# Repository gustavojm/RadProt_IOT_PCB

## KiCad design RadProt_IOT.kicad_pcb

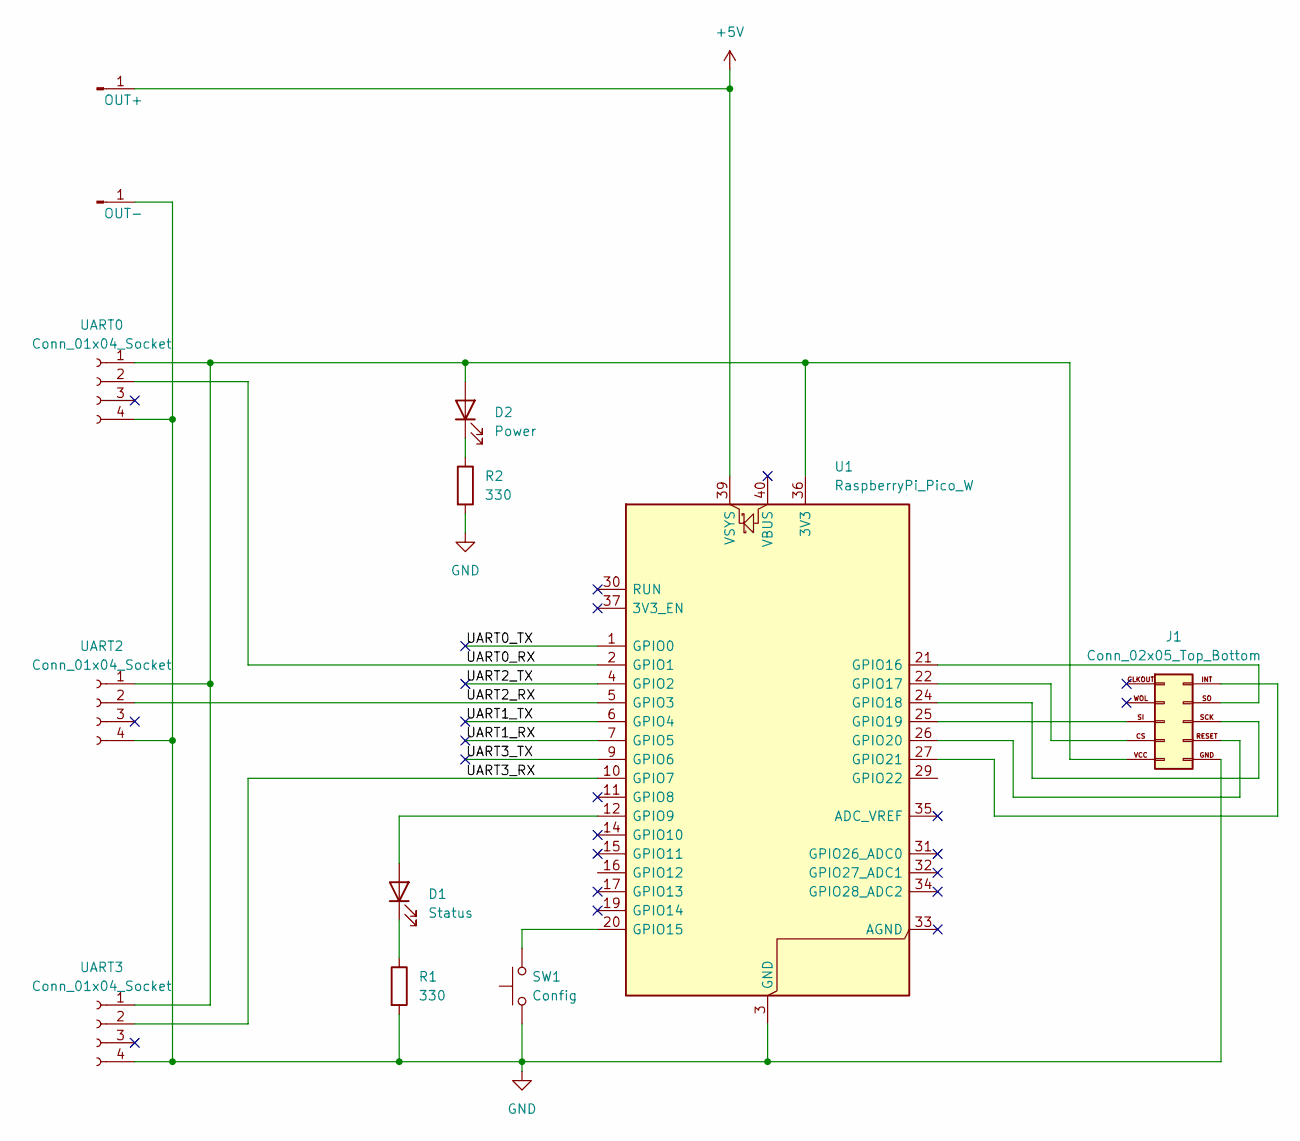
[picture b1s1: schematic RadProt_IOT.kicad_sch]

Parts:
D1: Status; LED_D3.0mm
D2: Power; LED_D3.0mm
J1: Conn_02x05_Top_Bottom; PinSocket_2x05_P2.54mm_Vertical
J5: OUT+; PinHeader_1x01_P2.54mm_Vertical
J6: OUT-; PinHeader_1x01_P2.54mm_Vertical
R1, R2: 330; R_Axial_DIN0204_L3.6mm_D1.6mm_P7.62mm_Horizontal
SW1: Config; SW_PUSH_6mm
U1: RaspberryPi_Pico_W; RaspberryPi_Pico_W_SMD_HandSolder
UART0, UART2, UART3: Conn_01x04_Socket; PinSocket_1x04_P2.54mm_Vertical

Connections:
+5V: J5.1, U1.39 (VSYS)
/UART0_RX: U1.2 (GPIO1), UART0.2
/UART0_TX: U1.1 (GPIO0)
/UART1_RX: U1.7 (GPIO5)
/UART1_TX: U1.6 (GPIO4)
/UART2_RX: U1.5 (GPIO3), UART2.2
/UART2_TX: U1.4 (GPIO2)
/UART3_RX: U1.10 (GPIO7), UART3.2
/UART3_TX: U1.9 (GPIO6)
GND: J1.GND, J6.1, R1.2, R2.2, SW1.1, U1.3 (GND), U1.8 (GND), U1.13 (GND), U1.18 (GND), U1.23 (GND), U1.28 (GND), U1.38 (GND), UART0.4, UART2.4, UART3.4
unnamed: D1.2 (A), U1.12 (GPIO9)
unnamed: D1.1 (K), R1.1
unnamed: D2.2 (A), J1.VCC, U1.36 (3V3), UART0.1, UART2.1, UART3.1
unnamed: D2.1 (K), R2.1
unnamed: SW1.2, U1.20 (GPIO15)
unnamed: J1.SO, U1.21 (GPIO16)
unnamed: J1.CS, U1.22 (GPIO17)
unnamed: J1.SCK, U1.24 (GPIO18)
unnamed: J1.SI, U1.25 (GPIO19)
unnamed: J1.RESET, U1.26 (GPIO20)
unnamed: J1.INT, U1.27 (GPIO21)

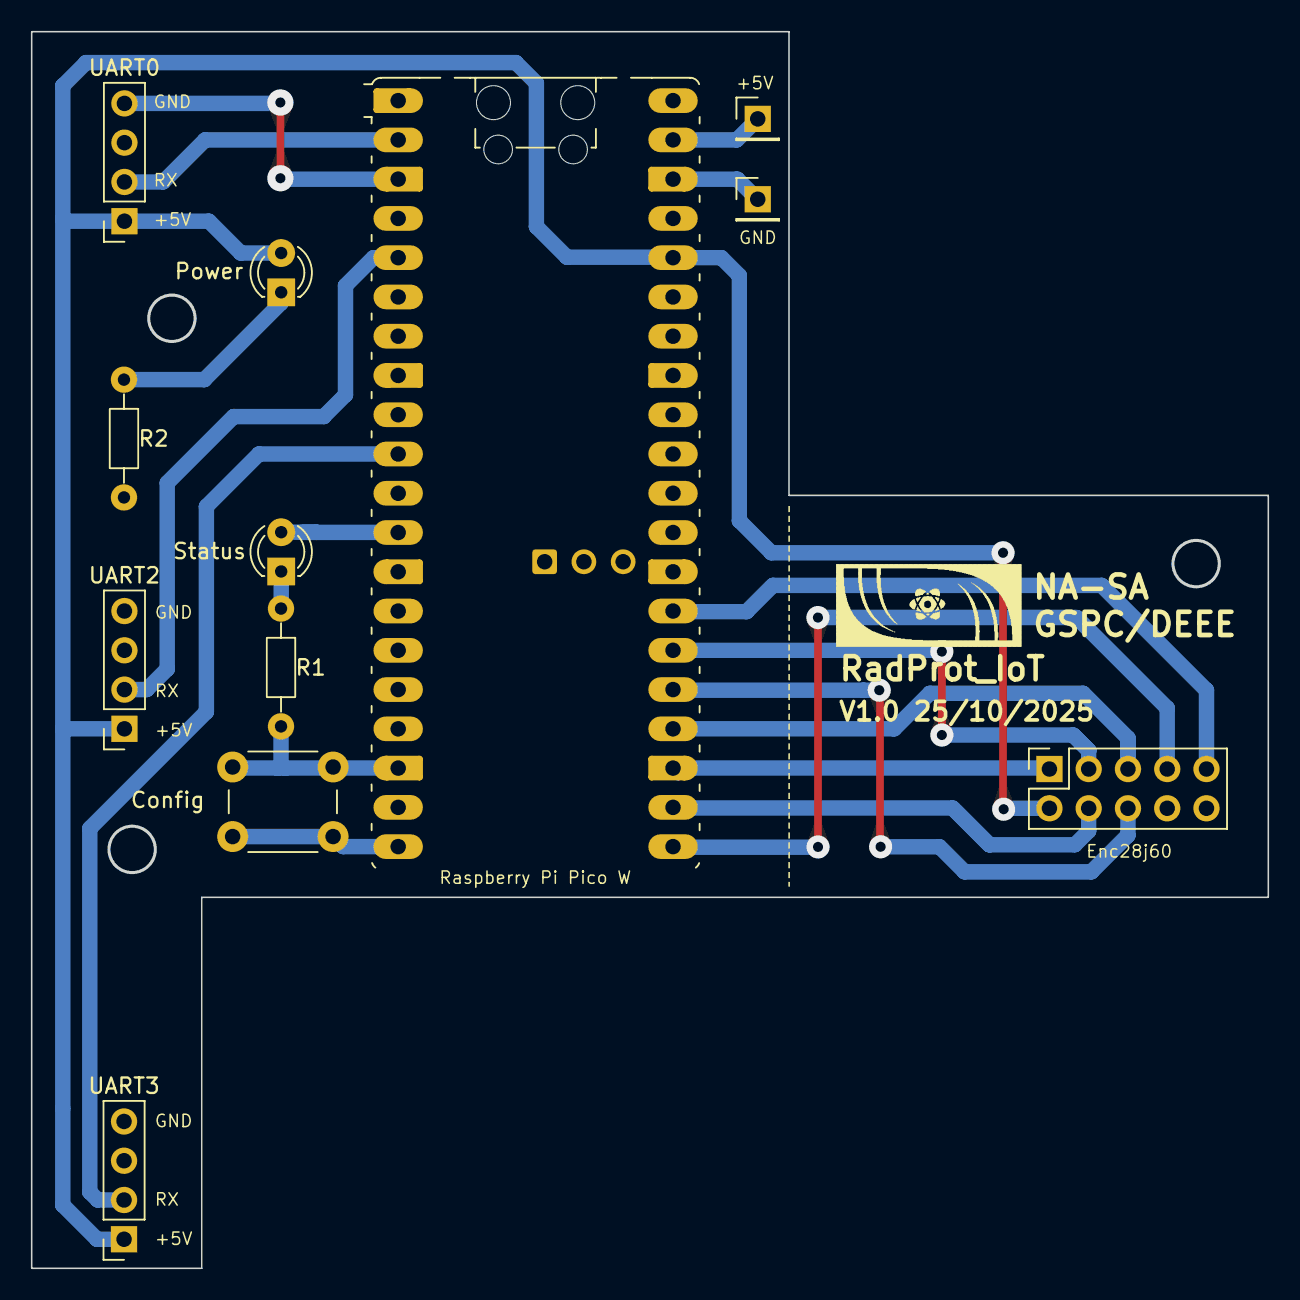
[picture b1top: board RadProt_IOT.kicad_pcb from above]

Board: 2 copper layers, 79.9 x 79.9 mm, 13 parts (0 on the bottom side), 16 nets.

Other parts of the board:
LOGO: logo_nasa

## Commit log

2025-06-25 manually routed, 1 route needs bridge
2025-06-26 routed with 1mm
2025-06-26 nice
2025-06-26 nicer
2025-06-26 nicer +10
2025-06-27 nice +20
2025-06-27 nice +30
2025-06-27 nice +40
2025-07-01 teardrops
2025-07-08 gcode generated...
2025-07-23 prepared univprepared universal board with this layout
2025-07-29 modified one pad of raspberry pi
2025-07-29 added Power Ledd
2025-07-31 to Cristian
2025-10-08 powering max3232's from 3V3 (RPi Pico's internal SMPS)
2025-10-08 changed some labels
2025-10-27 added logo and changed hole sizes from 0.65 to 0.8
2025-10-27 chgerbers generated
2025-10-27 changed layer selection on plot_on_all_layers
2025-11-11 connectors and sockets to 1mm
